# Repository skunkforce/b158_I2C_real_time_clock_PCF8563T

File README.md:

# edgy_board number b158
This design is part of the [edgy board project](https://github.com/skunkforce/edgy_boards). It provides a real-time clock PCF8563T.

# getting started
This repository uses submodules. After cloning use the command 

```$ git submodule update --init --recursive```

to pull the submodules before opening the project with kicad. 

# Tests
Tests can be found in [TESTS.md](TESTS.md)

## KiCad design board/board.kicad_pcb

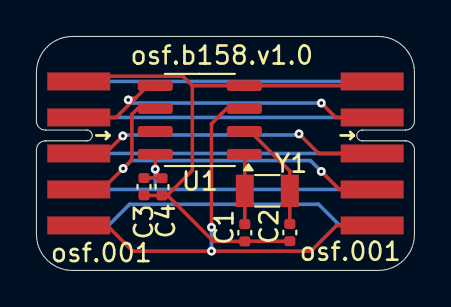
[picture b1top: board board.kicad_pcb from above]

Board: 2 copper layers, 21.0 x 13.0 mm, 8 parts (0 on the bottom side), 12 nets.

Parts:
C1, C2: 12pF; C_0402_1005Metric
C3: 100nF; C_0402_1005Metric
C4: 1uF; C_0402_1005Metric
J1: 001_I2C; on_edge_2x05_device
J2: 001_I2C; on_edge_2x05_host
U1: PCF8563T; SOIC-8_3.9x4.9mm_P1.27mm
Y1: 32.768kHz; Crystal_SMD_3215-2Pin_3.2x1.5mm

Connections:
/rtc/SCL: J1.4 (SCL), J2.4 (SCL), U1.6 (SCL)
/rtc/SDA: J1.2 (SDA), J2.2 (SDA), U1.5 (SDA)
/rtc/VDD: C3.1, C4.2, J1.9 (3.3V), J2.9 (3.3V), U1.8 (VDD)
/rtc/~INT: J1.5 (INT), J2.5 (INT), U1.3 (~INT)
GND: C1.1, C2.1, C3.2, C4.1, J1.1 (GND), J2.1 (GND), U1.4 (VSS)
unnamed: J1.10 (5V), J2.10 (5V)
unnamed: J1.6 (CS/EN), J2.6 (CS/EN)
unnamed: J1.3 (N/C), J2.3 (N/C)
unnamed: J1.7 (status), J2.7 (status)
unnamed: J1.8 (~RESET), J2.8 (~RESET)
unnamed: C1.2, U1.1 (OSCI), Y1.2
unnamed: C2.2, U1.2 (OSCO), Y1.1

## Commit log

2024-12-26 initial design
